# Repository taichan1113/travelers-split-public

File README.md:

[日本語](#日本語) / [English](#english)

# Travelers Split Public

## English

Public KiCad release bundle for the Travelers Split keyboard hardware.

### Projects

- `split_L_v2/ULP_Keyboard_split_L.kicad_pro`
- `split_R_v2/ULP_Keyboard_split_R.kicad_pro`
- `split_prog/ULP_Keyboard_split_prog.kicad_pro`

### Libraries

Project-local KiCad tables reference the bundled libraries under `libraries/` via `${KIPRJMOD}/../libraries/...`, so the projects can be opened without setting `KICAD_USER_LOCAL`.

### Repository Layout

- `split_L_v2/`: left half KiCad project
- `split_R_v2/`: right half KiCad project
- `split_prog/`: programmer KiCad project
- `libraries/`: symbols, footprints, and 3D models used by the projects

## 日本語

Travelers Split keyboard hardware の公開用 KiCad リリース一式です。

### プロジェクト

- `split_L_v2/ULP_Keyboard_split_L.kicad_pro`
- `split_R_v2/ULP_Keyboard_split_R.kicad_pro`
- `split_prog/ULP_Keyboard_split_prog.kicad_pro`

### ライブラリ

各プロジェクト内の KiCad ライブラリテーブルは、同梱の `libraries/` を `${KIPRJMOD}/../libraries/...` として参照します。そのため、`KICAD_USER_LOCAL` を設定しなくてもプロジェクトを開けます。

### リポジトリ構成

- `split_L_v2/`: 左手側の KiCad プロジェクト
- `split_R_v2/`: 右手側の KiCad プロジェクト
- `split_prog/`: 書き込み器用の KiCad プロジェクト
- `libraries/`: 各プロジェクトで使用するシンボル、フットプリント、3Dモデル

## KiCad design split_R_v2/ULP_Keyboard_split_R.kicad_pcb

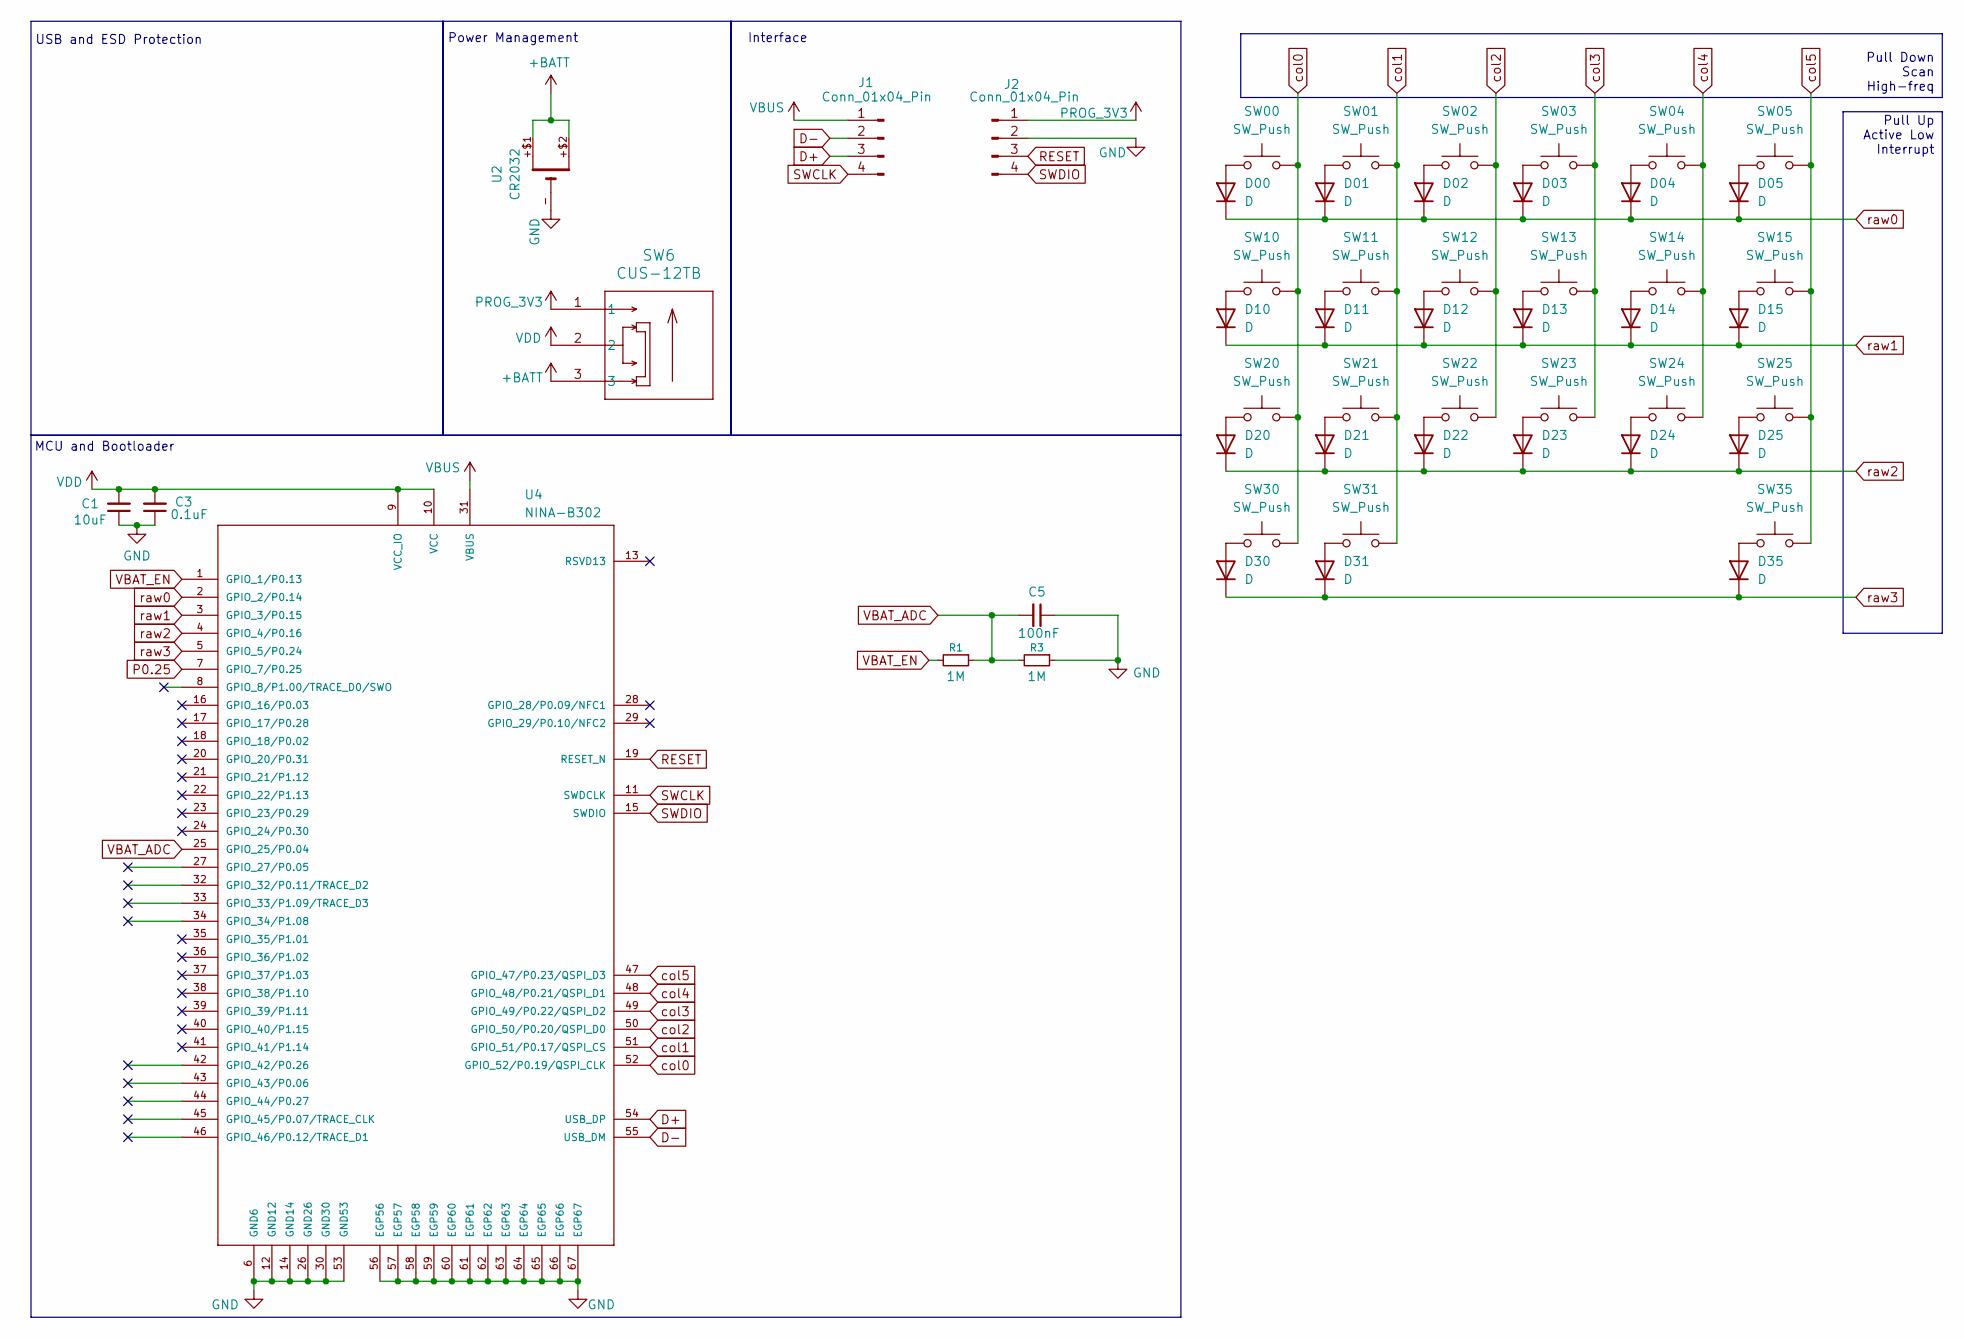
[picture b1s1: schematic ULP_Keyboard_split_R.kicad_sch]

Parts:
C1: 10uF; C_0603_1608Metric_Pad1.08x0.95mm_HandSolder; LCSC C19702
C3: 0.1uF; C_0603_1608Metric_Pad1.08x0.95mm_HandSolder; LCSC C14663
C5: 100nF; C_0603_1608Metric_Pad1.08x0.95mm_HandSolder; LCSC C14663
D00, D01, D02, D03, D04, D05, D10, D11, D12, D13, D14, D15, D20, D21, D22, D23, D24, D25, D30, D31, D35: D; Nexperia_CFP3_SOD-123W; LCSC C81598
J1, J2: Conn_01x04_Pin; ConnThrough_1x04
R1, R3: 1M; R_0603_1608Metric_Pad0.98x0.95mm_HandSolder; LCSC C22935
SW00, SW01, SW02, SW03, SW04, SW10, SW11, SW12, SW13, SW14, SW20, SW21, SW22, SW23, SW24, SW30, SW31: SW_Push; Kailh_socket_PG1316S_my_SMD
SW05, SW15, SW25, SW35: SW_Push; Kailh_socket_PG1316M_my_SMD
SW6: CUS-12TB; CUS12TB
U2: CR2032; CR2032-SMD-BH67D5
U4: NINA-B302; NINA_302_my; PART_DESCRIPTION Stand-alone Bluetooth low energy module

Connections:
+BATT: SW6.3, U2.+$1, U2.+$2
D+: J1.3, U4.54 (USB_DP)
D-: J1.2, U4.55 (USB_DM)
GND: C1.1, C3.1, C5.1, J2.2, R3.1, U2.-, U4.6 (GND6), U4.12 (GND12), U4.14 (GND14), U4.26 (GND26), U4.30 (GND30), U4.53 (GND53), U4.56 (EGP56), U4.57 (EGP57), U4.58 (EGP58), U4.59 (EGP59), U4.60 (EGP60), U4.61 (EGP61), U4.62 (EGP62), U4.63 (EGP63), U4.64 (EGP64), U4.65 (EGP65), U4.66 (EGP66), U4.67 (EGP67)
unnamed: D00.2 (A), SW00.1
unnamed: D01.2 (A), SW01.1
unnamed: D02.2 (A), SW02.1
unnamed: D03.2 (A), SW03.1
unnamed: D04.2 (A), SW04.1
unnamed: D05.2 (A), SW05.1
unnamed: D10.2 (A), SW10.1
unnamed: D11.2 (A), SW11.1
unnamed: D12.2 (A), SW12.1
unnamed: D13.2 (A), SW13.1
unnamed: D14.2 (A), SW14.1
unnamed: D15.2 (A), SW15.1
unnamed: D20.2 (A), SW20.1
unnamed: D21.2 (A), SW21.1
unnamed: D22.2 (A), SW22.1
unnamed: D23.2 (A), SW23.1
unnamed: D24.2 (A), SW24.1
unnamed: D25.2 (A), SW25.1
unnamed: D30.2 (A), SW30.1
unnamed: D31.2 (A), SW31.1
unnamed: D35.2 (A), SW35.1
P0.25: U4.7 (GPIO_7/P0.25)
PROG_3V3: J2.1, SW6.1
RESET: J2.3, U4.19 (RESET_N)
SWCLK: J1.4, U4.11 (SWDCLK)
SWDIO: J2.4, U4.15 (SWDIO)
VBAT_ADC: C5.2, R1.1, R3.2, U4.25 (GPIO_25/P0.04)
VBAT_EN: R1.2, U4.1 (GPIO_1/P0.13)
VBUS: J1.1, U4.31 (VBUS)
VDD: C1.2, C3.2, SW6.2, U4.9 (VCC_IO), U4.10 (VCC)
col0: SW00.2, SW10.2, SW20.2, SW30.2, U4.52 (GPIO_52/P0.19/QSPI_CLK)
col1: SW01.2, SW11.2, SW21.2, SW31.2, U4.51 (GPIO_51/P0.17/QSPI_CS)
col2: SW02.2, SW12.2, SW22.2, U4.50 (GPIO_50/P0.20/QSPI_D0)
col3: SW03.2, SW13.2, SW23.2, U4.49 (GPIO_49/P0.22/QSPI_D2)
col4: SW04.2, SW14.2, SW24.2, U4.48 (GPIO_48/P0.21/QSPI_D1)
col5: SW05.2, SW15.2, SW25.2, SW35.2, U4.47 (GPIO_47/P0.23/QSPI_D3)
raw0: D00.1 (K), D01.1 (K), D02.1 (K), D03.1 (K), D04.1 (K), D05.1 (K), U4.2 (GPIO_2/P0.14)
raw1: D10.1 (K), D11.1 (K), D12.1 (K), D13.1 (K), D14.1 (K), D15.1 (K), U4.3 (GPIO_3/P0.15)
raw2: D20.1 (K), D21.1 (K), D22.1 (K), D23.1 (K), D24.1 (K), D25.1 (K), U4.4 (GPIO_4/P0.16)
raw3: D30.1 (K), D31.1 (K), D35.1 (K), U4.5 (GPIO_5/P0.24)

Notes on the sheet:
Interface
MCU and Bootloader
Pull Down Scan High-freq
Power Management
Pull Up Active Low Interrupt
USB and ESD Protection

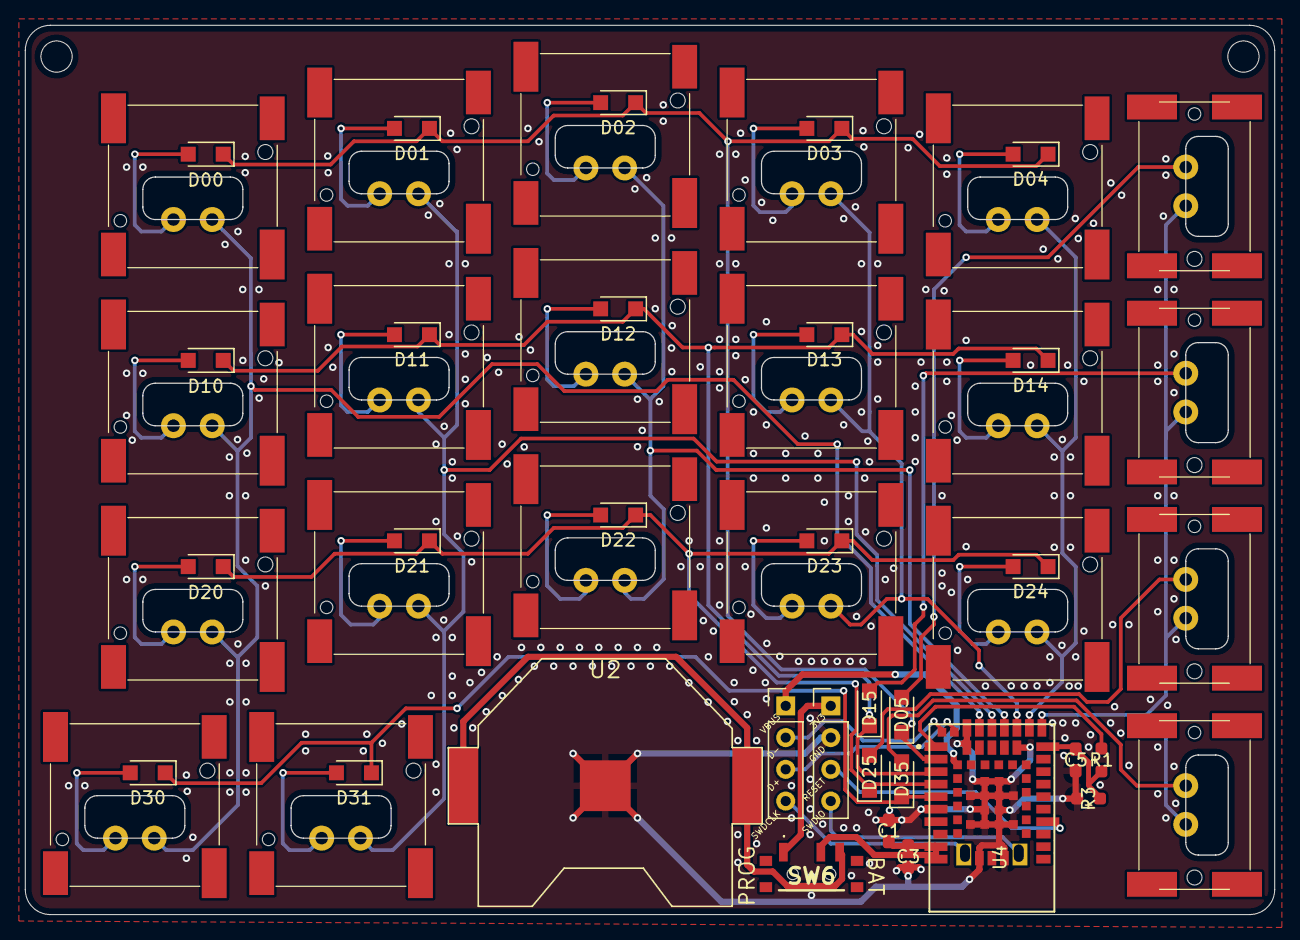
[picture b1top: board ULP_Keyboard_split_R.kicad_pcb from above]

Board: 2 copper layers, 100.0 x 71.2 mm, 52 parts (0 on the bottom side), 43 nets.

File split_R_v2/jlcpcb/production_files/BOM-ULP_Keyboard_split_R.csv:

Comment,Designator,Footprint,LCSC,Quantity
0.1uF,"C3,C5",C_0603_1608Metric_Pad1.08x0.95mm_HandSolder,C14663,2
10uF,C1,C_0603_1608Metric_Pad1.08x0.95mm_HandSolder,C19702,1
1M,"R1,R3",R_0603_1608Metric_Pad0.98x0.95mm_HandSolder,C22935,2
D,"D00,D01,D02,D03,D04,D05,D10,D11,D12,D13,D14,D15,D20,D21,D22,D23,D24,D25,D30,D31,D35",Nexperia_CFP3_SOD-123W,C81598,21

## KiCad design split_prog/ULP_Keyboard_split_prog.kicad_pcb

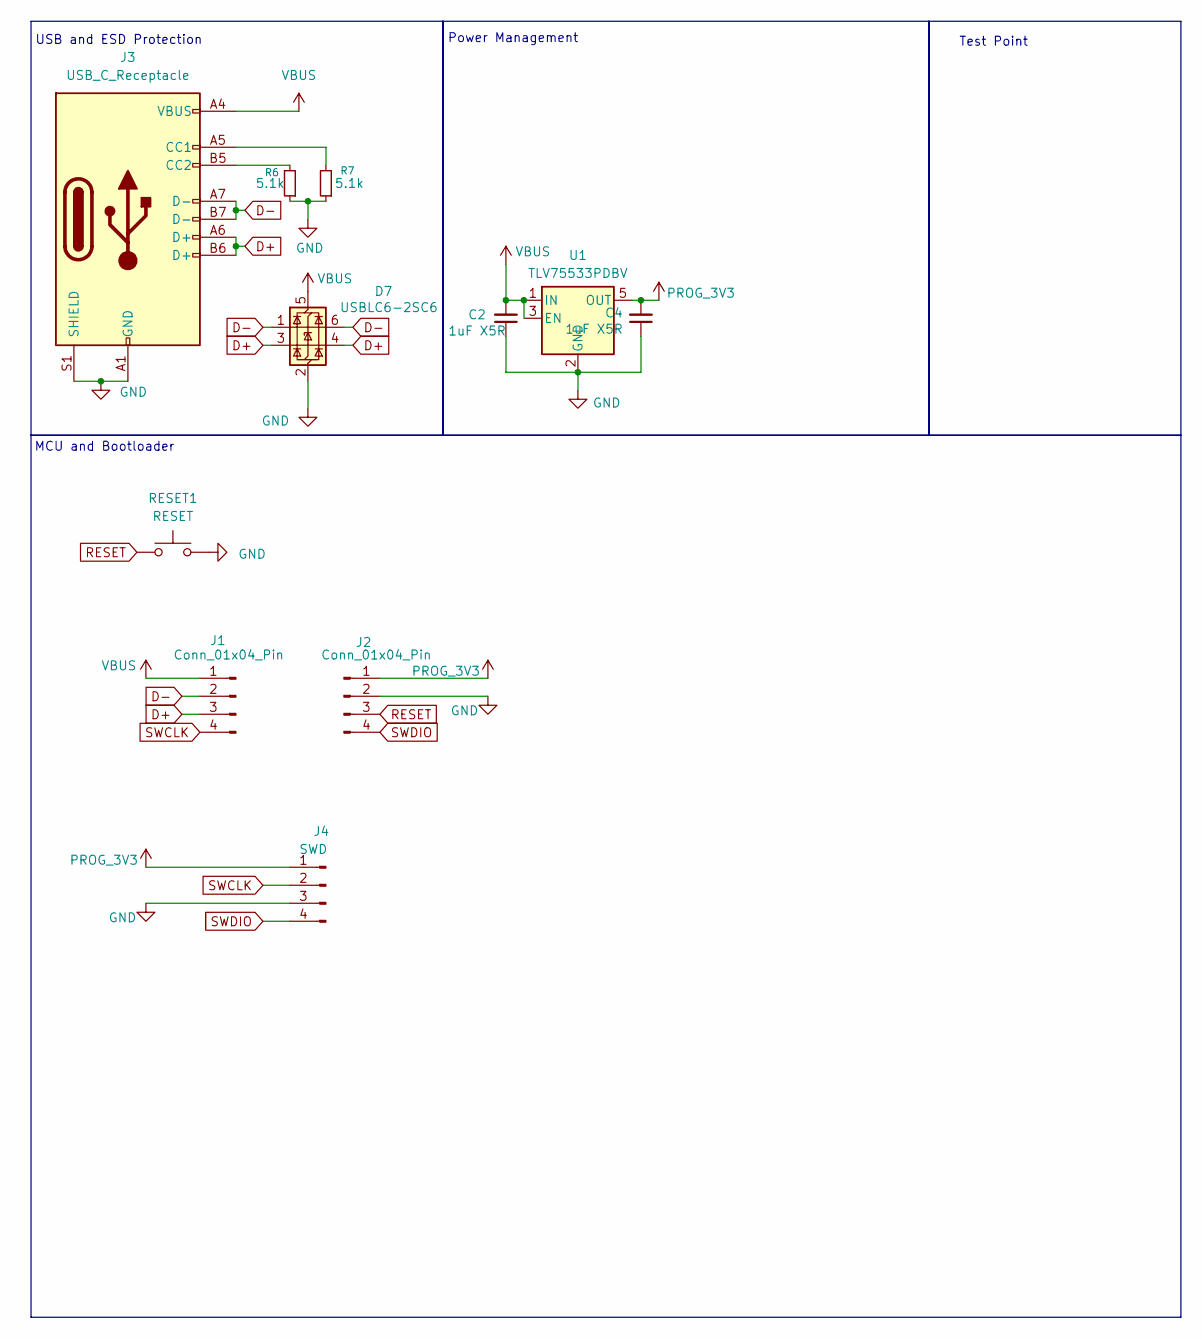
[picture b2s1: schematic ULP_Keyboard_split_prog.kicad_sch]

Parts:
C2, C4: 1uF X5R; C_0603_1608Metric_Pad1.08x0.95mm_HandSolder; LCSC C19702
D7: USBLC6-2SC6; SOT-23-6; LCSC C7519
J1, J2: Conn_01x04_Pin; ConnThrough_1x04
J3: USB_C_Receptacle; USB_C_Receptacle_HRO_TYPE-C-31-M-12
J4: SWD; JST_SH_BM04B-SRSS-TB_1x04-1MP_P1.00mm_Vertical
R6, R7: 5.1k; R_0603_1608Metric_Pad0.98x0.95mm_HandSolder; LCSC C23186
RESET1: RESET; SW_SPST_TL3342
U1: TLV75533PDBV; SOT-23-5; LCSC C404027

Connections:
D+: D7.3 (I/O2), D7.4 (I/O2), J1.3, J3.A6 (D+), J3.B6 (D+)
D-: D7.1 (I/O1), D7.6 (I/O1), J1.2, J3.A7 (D-), J3.B7 (D-)
GND: C2.1, C4.1, D7.2 (GND), J2.2, J3.A1 (GND), J3.A12 (GND), J3.B1 (GND), J3.B12 (GND), J3.S1 (SHIELD), J4.3, R6.1, R7.1, RESET1.2, U1.2 (GND)
unnamed: J3.A5 (CC1), R7.2
unnamed: J3.B5 (CC2), R6.2
PROG_3V3: C4.2, J2.1, J4.1, U1.5 (OUT)
RESET: J2.3, RESET1.1
SWCLK: J1.4, J4.2
SWDIO: J2.4, J4.4
VBUS: C2.2, D7.5 (VBUS), J1.1, J3.A4 (VBUS), J3.A9 (VBUS), J3.B4 (VBUS), J3.B9 (VBUS), U1.1 (IN), U1.3 (EN)

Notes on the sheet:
Test Point
MCU and Bootloader
Power Management
USB and ESD Protection

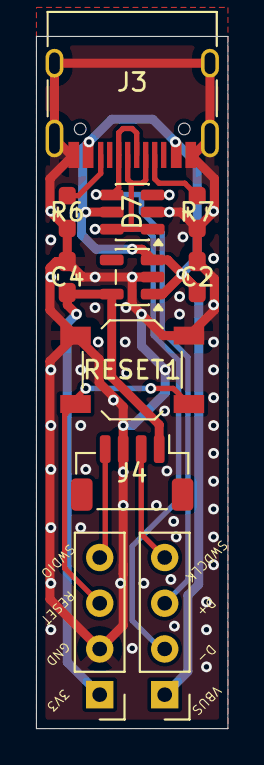
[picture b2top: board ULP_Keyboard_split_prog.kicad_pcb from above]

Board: 2 copper layers, 10.6 x 38.5 mm, 11 parts (0 on the bottom side), 10 nets.

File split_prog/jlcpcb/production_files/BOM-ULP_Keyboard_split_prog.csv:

Comment,Designator,Footprint,LCSC,Quantity
1uF X5R,"C2,C4",C_0603_1608Metric_Pad1.08x0.95mm_HandSolder,C19702,2
5.1k,"R6,R7",R_0603_1608Metric_Pad0.98x0.95mm_HandSolder,C23186,2
TLV75533PDBV,U1,SOT-23-5,C404027,1
USBLC6-2SC6,D7,SOT-23-6,C7519,1
